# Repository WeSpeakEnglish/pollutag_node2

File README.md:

# Pollutag Node2
The LoraWAN node for air quatity monitoring based on STM32WLE and SEN54 Sensirion sensor
868 Mhz LoRaWAN node for continuous air quality monitoring. The node operates autonomously and support remote commands via downlinks.
SEN54 connected via I2C2 interface.
1. LaraWAN node based on STM32WLE MCU (LORA-E5), easy to integrate monitoring and control node (air quality monitoring, garden, intelligent home. etc.)
2. You may connect load remotely by downlinks - via AO3400A transistor (on board)
3. New Sensirion SEN54 sensor optimized
4. MPPT and Li-Ion battery charger for power from 5V++ cheap solar panels.
5. Sleep current as low as 0.9 mA
6. 10+ years of autonomity with cheap 2W solar panel and standard 1850 Li-Ion battery
7. More than 2 weeks work autonomity from fully charged 3500mA  Li-Ion battery
8. Ideal for sensor.community integration over LoRaWAN IoT, like TTN and Helium, no internet connection from your side needed!
9. Full fledged with routed test points - easy to solder - easy to add functionality (inputs, outputs, interfaces etc.)

## How the node works (firmware v1.4.1)
Measurement cycle (default every 30 minutes, set by downlink `02`):

| Time | Action |
|---|---|
| 0 s | SEN54 power on (skipped while the battery level byte is 143 or lower) |
| 1 s | Sensor reset, VOC algorithm state restored, measurement started |
| 31-60 s | PM: 30 s start-up, then one sample per second averaged over 30 s (Sensirion "Reduced Power Operation SEN5x" recommendation). VOC, temperature and humidity are taken from the last sample |
| 61 s | Result ready; uplink sent if no uplink period is set |
| 62 s | VOC algorithm state saved, measurement stopped |
| 63 s | SEN54 power off |

The sensor is powered for 63 s per cycle (about 70 mA while measuring).
VOC note: the SEN54 VOC index learns its baseline during continuous operation. Because the sensor is
powered off between measurements, the VOC value is only a rough, short-term indicator. The VOC
algorithm state is saved before power-off and restored at power-up to reduce the effect.

Uplinks are unconfirmed, with ADR on. By default one uplink is sent after each measurement; with
downlink `03` the node sends instead on its own timer (each uplink carries the latest measurement).
If the duty-cycle limit does not allow sending yet, the LoRaWAN stack queues the uplink and sends it
as soon as allowed. Settings made by downlink are not stored: after a reset the defaults apply again.

## Downlink commands supported
All commands on Port 2, two bytes `[command, value]` (except reset):

| Downlink | Command | Value |
|---|---|---|
| `01 00` / `01 01` | LED / load output off / on | This LED is enhanced with a FET transistor, so you may connect some load to be switched ON/OFF (see the schematic in PCB folder) |
| `02 XX` | Measuring period | XX minutes (hex). `00` = measuring off, `01` is raised to the 2 minute minimum. Default 30 min (`02 1E`) |
| `03 XX` | Uplink period | XX minutes (hex), minimum 1. Uplinks are then sent only every XX minutes. `00` = one uplink after each measurement (default) |
| `FF FF FF FF FF FF` | Reset the device | |

Examples: `02 3C` measure every 60 min, `03 05` send every 5 min, `01 01` LED on.

Downlink payload encoder example:
```js
function Encoder(measurements, port) {
    // LED on/off
    if (measurements.LED_ON !== undefined) return [0x01, measurements.LED_ON.value ? 1 : 0];
    // measuring period, minutes (0 = off)
    if (measurements.MEASURE_MIN !== undefined) return [0x02, measurements.MEASURE_MIN.value & 0xFF];
    // uplink period, minutes (0 = after each measurement)
    if (measurements.UPLINK_MIN !== undefined) return [0x03, measurements.UPLINK_MIN.value & 0xFF];
    return [];
}
```
## Uplink
The node uplink data packet (Port 2) contains 14 payload bytes with the following data: PM1 concentration,
PM2.5 concentration, PM10 concentration (30 s averages), temperature, humidity, volatile organic compounds
index (VOC), battery level related to volts, status of LED output.

| Bytes | Value | Encoding | Invalid / no data |
|---|---|---|---|
| 0-1 | PM1.0 | ug/m3 x10, big endian | `FF FF` |
| 2-3 | PM2.5 | ug/m3 x10, big endian | `FF FF` |
| 4-5 | PM10 | ug/m3 x10, big endian | `FF FF` |
| 6-7 | Temperature | byte6 + byte7/100 - 100 [degC] | `FF FF` |
| 8-9 | Humidity | byte8 + byte9/100 [%RH] | `FF FF` |
| 10-11 | VOC index | x10, big endian | `FF FF` |
| 12 | Battery level | x 0.0238 = volts | |
| 13 | LED output | 0 = off, 1 = on | |

Invalid values are sent when the sensor did not answer or had no data (for example while the battery is
too low to power it).

Decoder for payload on server side (uplink):
```js
 function Decoder(bytes, port, uplink_info) {
    var decoded = {};
    function u16(i) { return bytes[i]*256 + bytes[i+1]; }
    function invalid(i) { return bytes[i] === 0xFF && bytes[i+1] === 0xFF; }
    decoded.PM1   = invalid(0) ? null : (u16(0)/10.0).toFixed(2);
    decoded.PM2_5 = invalid(2) ? null : (u16(2)/10.0).toFixed(2);
    decoded.PM10  = invalid(4) ? null : (u16(4)/10.0).toFixed(2);
    decoded.T     = invalid(6) ? null : (-100.0 + bytes[6] + bytes[7]/100.0).toFixed(2);
    decoded.RH    = invalid(8) ? null : (bytes[8] + bytes[9]/100).toFixed(2);
    decoded.VOC   = invalid(10) ? null : (u16(10)/10.0).toFixed(2);
    decoded.Battery = (bytes[12]*0.0238).toFixed(2);//battery , volts
    decoded.LEDON = bytes[13];
    decoded.RSSI = normalizedPayload.gateways[0].rssi.toFixed(0);
    decoded.SNR = normalizedPayload.gateways[0].snr.toFixed(0);
    decoded.FREQUENCY = normalizedPayload.frequency;
    return decoded;
 }
```

## Open and build
1. Install STM32CubeIDE (the `.ioc` was saved with STM32CubeMX 6.15, firmware package STM32Cube FW_WL V1.3.1).
2. *File > Import > General > Existing Projects into Workspace*, select the `FW` folder. The project is called `pollutag_node2`.
3. Build: *Debug* (no optimisation, for debugging) or *Release* (optimised, for deployment).
   All sources, include paths and the linker script are relative to the project folder, so no setup is needed.
4. Flash / debug with the `pollutag_node2` launch configuration (ST-LINK, connect under reset).

Notes:
- The firmware package FW_WL V1.3.1 is only needed to regenerate code from the `.ioc`; building works without it.
- Application code lives in `FW/Core/Src/app_sensor.c` (sensor and measurement cycle) and `FW/LoRaWAN/App/lora_app.c`
  (uplink payload, downlinks), inside the CubeMX `USER CODE` sections so regenerating keeps it.
- The last 4 KB of flash (0x0803F000) hold the LoRaWAN session and are reserved in `FW/STM32WLE5JCIX_FLASH.ld`.
- Enter the LoRaWAN credentials of your device in `FW/LoRaWAN/App/lorawan_credentials.h` before building, see [LoRaWAN credentials](#lorawan-credentials).

## Preparation
Originally LORA-E5 (Wio)  modules came pre-programmed with AT-command enabled stack, working like a LoRaWAN modem.
To use the core MCU for this node it is needed first to erase the chip and prepare the project for proper comissioning. You may use commissioning identificators already pre-programmed into the chip by Seeed studio, or generate the new via TTN/ Helium console.
To erase chip connect it via ST-LINK **under reset** (you need to short RESET pin (J1, pin 5) of the MCU to the ground before you press "Connect" button in STM32CubeProgrammer).

After you successfully connected the MCU, it need to be reprogrammed Read protection Option Byte to AA (no protection)

After completing this process, the chip should be successfully cleaned.

## LoRaWAN credentials
The keys are **not** taken from the `.ioc` (it keeps zeros). Each device has its own small file
`FW/LoRaWAN/App/lorawan_credentials.h`, which overrides the CubeMX values and survives code regeneration:

```c
#define LORAWAN_DEVICE_EUI    00,00,00,00,00,00,00,00                          // 8 bytes
#define LORAWAN_JOIN_EUI      00,00,00,00,00,00,00,00                          // 8 bytes (AppEUI)
#define LORAWAN_APP_KEY       00,00,00,00,00,00,00,00,00,00,00,00,00,00,00,00  // 16 bytes
```

1. Copy `FW/LoRaWAN/App/lorawan_credentials_template.h` to `FW/LoRaWAN/App/lorawan_credentials.h`
   (if the file is missing the build stops with a message saying so).
2. Enter the values from your network console (TTN, Helium, ChirpStack...) as comma separated hex
   bytes, MSB first, exactly as the console shows them.
3. Build and flash. At boot the node prints the `DevEUI` and `JoinEUI` it uses on the debug UART (115200 baud).

Options:
- `LORAWAN_DEVICE_EUI` all `00`: the DevEUI is derived from the MCU unique ID. Read it from the boot log
  and register the device with that DevEUI in the network console.
- `LORAWAN_JOIN_EUI` may be left all `00` for networks that accept it (useful if you plan to move to a
  different LoRaWAN network later: register the node on the new network console, reset the node, then
  delete it on the old console and reset again).
- You may also reuse the identifiers pre-programmed by Seeed Studio (read them out with the AT commands
  before erasing the chip).

`lorawan_credentials.h` is device specific and secret: do not share or commit it (it is listed in
`FW/.gitignore`); share `lorawan_credentials_template.h` instead.

Hackaday project: [LINK](https://hackaday.io/project/198348-pollutagnode2-air-quality-monitor-lorawan)

OSHWLab STD project: [LINK](https://oshwlab.com/pinelab/pollutagnode2-lorawan-node-air-quality-monitor)

OSHWLab PRO poject: [LINK](https://oshwlab.com/pinelab/pollutag2)

Pollutants.eu: [LINK](https://pollutants.eu/index.php/component/search/?searchword=pollutag&searchphrase=all&Itemid=121)

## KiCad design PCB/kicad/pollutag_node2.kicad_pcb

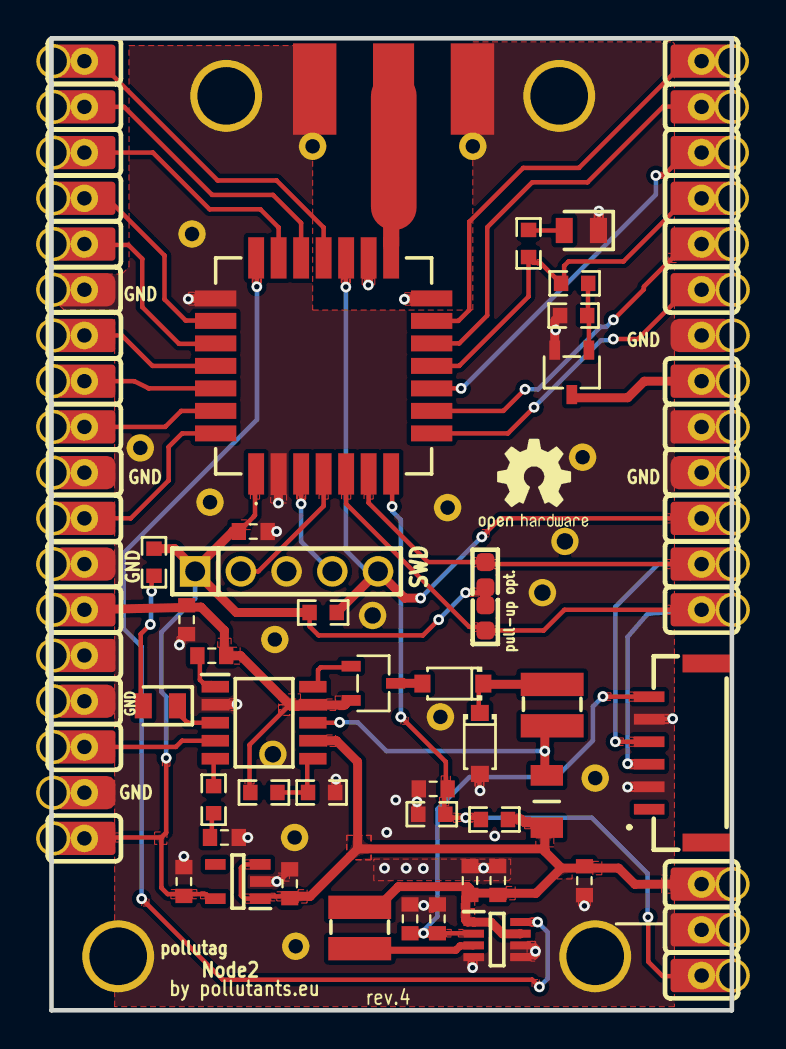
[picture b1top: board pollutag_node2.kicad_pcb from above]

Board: 2 copper layers, 37.8 x 54.0 mm, 65 parts (0 on the bottom side), 43 nets.

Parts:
3V3: S1751-46R
BAT+: S1751-46R
BAT-: S1751-46R
C1, C2, C3, C4, C5, C6, C7, C8, C9, C10, C11, C12: CAP0603
D1, D2: SOD-123_L2.6-W1.7-LS3.5-RD
DONE: S1751-46R
GND: S1751-46R
IC1: LORAE5
IC2: SOT65P280X100-8N
IC3: SOT95P280X145-5N
IC4: SOP100P600X175-10N
J1: HDR-TH_5P-P2.54-V-M
J2: 142-0701-801
J3: SM06B-GHS-TB
L1, L2: IND-SMD_L3.0-W3.0_SRN3015
LED1, LED2: LEDC2012X90N
LOAD: S1751-46R
PA0, PA2, PA3, PA10, PA15: S1751-46R
PB0, PB3, PB4, PB5, PB6, PB7, PB9, PB10, PB13, PB14, PB15: S1751-46R
PC0, PC1: S1751-46R
Q1, Q2: SOT-23-3_L2.9-W1.6-P1.90-LS2.8-BR
R1, R2, R4, R5, R6, R7, R8, R9, R10, R11: R0603
R3: RESC3216X70N
RST: S1751-46R
SOL+: S1751-46R
SOL-: S1751-46R

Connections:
3.3V: 3V3.1, C3.2, C5.2, IC1.1, IC3.5, J1.1, R2.2, R7.2
5V: C2.1, C12.2, IC2.2, J3.6
5V_EN: IC1.21, IC2.8
$1N6: IC1.11, PB5.1, R1.2, R10.2
$1N7: Q2.1, R10.1, R11.2
$1N11: IC4.3, LED2.1
$1N12: C11.2, IC1.7, PB4.1, R8.2, R9.1
$1N25: IC1.12, PC1.1
$1N26: IC1.13, PC0.1
$1N28: IC1.27, PA10.1
$1N29: IC1.18, PA3.1
$1N30: IC1.19, PA2.1
$1N31: IC1.23, PA0.1
$1N32: IC1.26, PB14.1
$1N33: IC1.24, PB13.1
$1N34: IC1.20, PB10.1
$1N35: IC1.25, PB9.1
$1N36: IC1.9, PB7.1
$1N37: IC1.10, PB6.1
$1N40: IC1.8, PB3.1
$1N50: LED1.2, R1.1
$1N57: IC2.3, L1.2
$1N60: C9.2, R5.2
$1N61: IC4.5, R5.1
$1N63: IC4.8, L2.2, R3.1
$1N64: D1.1, D2.1, L2.1
$1N72: D1.2, Q1.3
$1N73: IC4.10, Q1.1
$1N75: LED2.2, R7.1
$1N76: IC4.6, R4.1, R6.2
$1N77: IC1.28, PB0.1
$1N78: C6.2, IC4.1
$1N83: DONE.1, IC4.4
ANT: IC1.15, J2.2
BAT+: BAT+.1, C1.1, C4.2, C7.2, C10.2, IC2.1, IC2.7, IC3.1, IC3.3, IC4.7, L1.1, R3.2, R9.2
GND: BAT-.1, C1.2, C2.2, C3.1, C4.1, C5.1, C7.1, C8.1, C9.1, C10.1, C11.1, C12.1, D2.2, GND.1, IC1.2, IC1.14, IC1.16, IC1.22, IC2.4, IC2.5, IC2.6, IC3.2, IC4.2, J1.3, J2.1, J2.3, J3.2, J3.5, LED1.1, Q2.2, R6.1, R8.1, R11.1, SOL-.1
LOAD: LOAD.1, Q2.3
RST: IC1.17, J1.5, R2.1, RST.1
SEN_SCL: IC1.5, J3.3, PB15.1
SEN_SDA: IC1.6, J3.4, PA15.1
SOL: C6.1, C8.2, IC4.9, Q1.2, R4.2, SOL+.1
SWCLK: IC1.4, J1.2
SWDIO: IC1.3, J1.4

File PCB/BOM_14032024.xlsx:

Quantity | Comment | Description | Designator | Manufacturer_Name
6 | GRM188R61C106KAALD | Capacitor 10uF 0603, X5R | C1, C2, C3, C7, C8, C11 | Murata Electronics
4 | 06035C104KAT2A | Capacitor | C4, C5, C6, C10 | AVX
1 | AC0603KRX7R9BB224 | Capacitor | C9 | KEMET
2 | PMEG2010AEH | Diode | D1, D2 | Nexperia
1 | LoRa-E5 | Integrated Circuit | IC1 | Seeed Studio
1 | MPQ3413GJ-5-AEC1-P | Integrated Circuit | IC2 | Monolithic Power Systems (MPS)
1 | LDCL015M33R | Integrated Circuit | IC3 | STMicroelectronics
1 | CN3791 | Integrated Circuit | IC4 | Consonance
1 | 2355182-5 | Connector | J1 | TE Connectivity
1 | 142-0701-801 | Connector | J2 | Cinch Connectivity Solutions
1 | SM06B-GHS-TB_LF__SN_ | Connector | J3 | JST (JAPAN SOLDERLESS TERMINALS)
1 | SRN3015-2R2M | Inductor | L1 | Bourns
1 | SRN3015BTA-100M | Inductor | L2 | Bourns
2 | LTST-C171YKT | LED | LED1, LED2 | Lite-On
1 | PMV41XPAR | MOSFET (P-Channel) | Q1 | Nexperia
1 | AO3400A | MOSFET (N-Channel) | Q2 | Alpha & Omega Semiconductors
3 | RC0603FR-072KL | Resistor 2k 0603 | R1, R7, R10 | Yageo
4 | CR0603-FX-3002ELF | Resistor 30k 0603 | R2, R6, R8, R11 | Bourns
1 | CRL1206-FW-R100ELF | Resistor | R3 | Bourns
2 | RT0603FRE0782KL | Resistor | R4, R9 | KEMET
1 | ERJ-U03J121V | Resistor | R5 | Panasonic

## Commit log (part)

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2024-07-05 stable 3 moths run, commands works
2024-07-05 image added
2024-07-09 PCB added
2024-07-09 Readme fix
2024-09-29 Create LICENSE
2024-10-21 updated PCB gerbers for standarn 2.54mm step/ 0.8mm hole size for pin headers
2024-10-21 image updated
2025-02-06 Update README.md, links provided
2025-11-04 try OTAA
2025-11-04 OTAA corrected
2025-11-05 uplink works
2025-11-06 1.0.4 stack
2025-11-11 Refactor downlink payload encoder example in README
    Removed redundant downlink payload encoder example and added it in a new section.
2026-05-13 gerbs added
2026-05-13 added new image
